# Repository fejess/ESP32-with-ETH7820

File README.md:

# ESP32 with ETH7820AI

SIMPLE project with ETH7820 with ESP32, without PHY power and clock out.
Tested.

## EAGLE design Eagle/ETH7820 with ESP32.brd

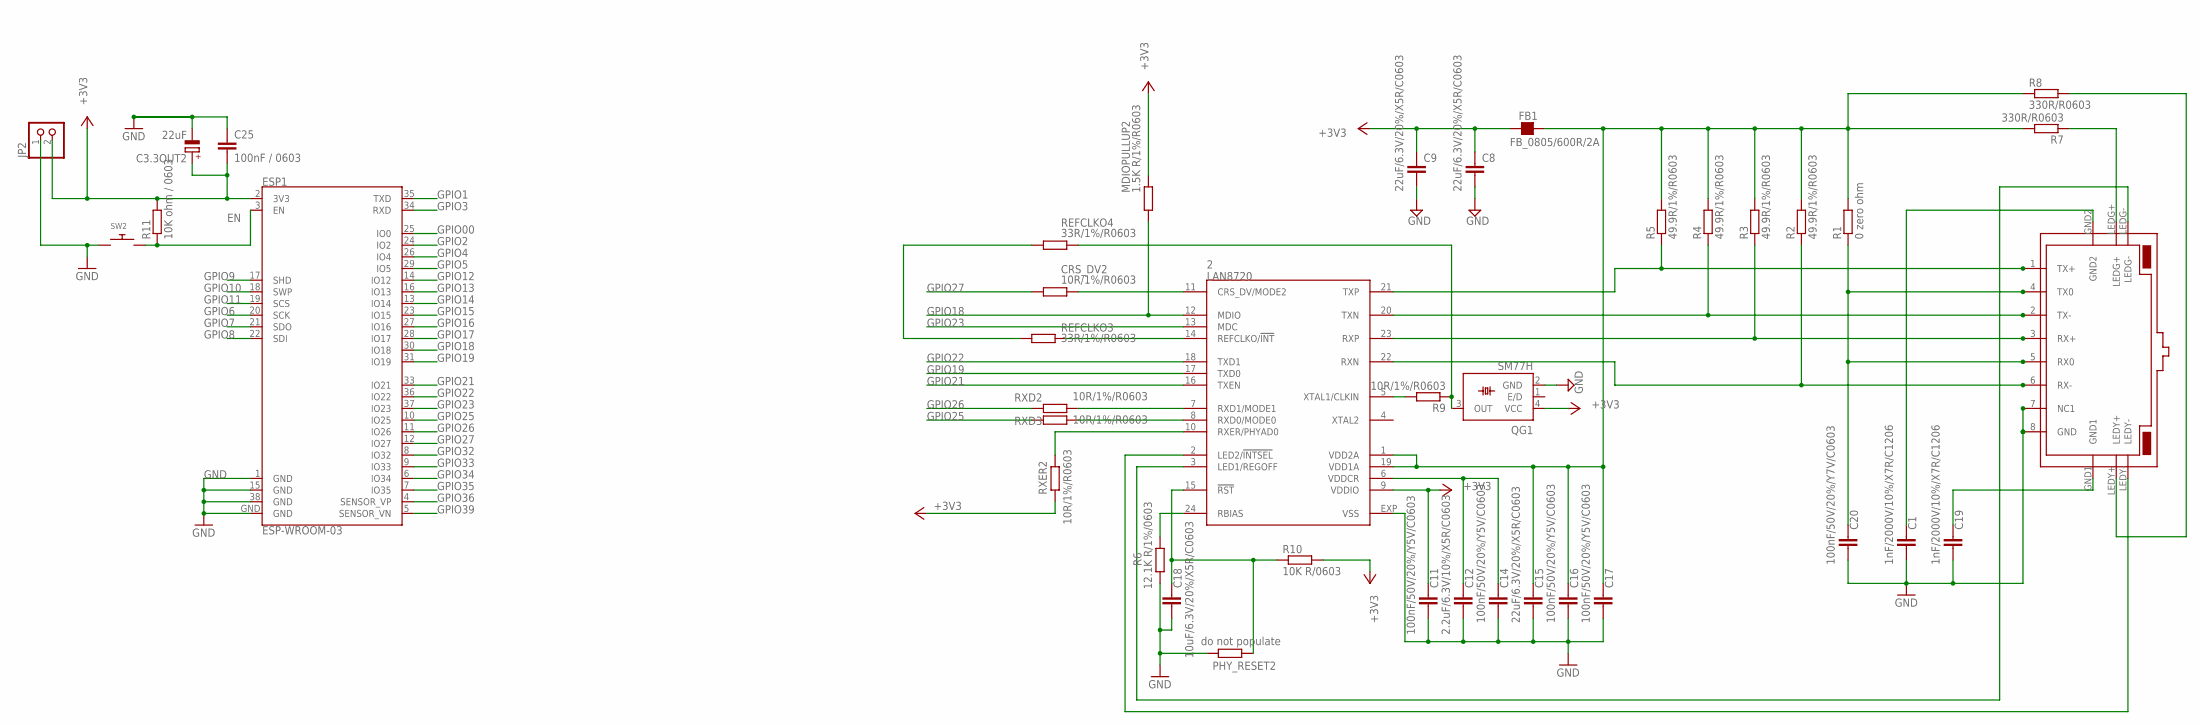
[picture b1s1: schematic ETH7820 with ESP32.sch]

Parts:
2: LAN8720; QFN24
C1, C19: 1nF/2000V/10%/X7R/C1206; C1206
C3.3OUT2: 22uF; 153CLV-0605
C8, C9, C15: 22uF/6.3V/20%/X5R/C0603; C0603
C11, C14, C16, C17: 100nF/50V/20%/Y5V/C0603; C0603
C12: 2.2uF/6.3V/10%/X5R/C0603; C0603
C18: 10uF/6.3V/20%/X5R/C0603; C0603
C20: 100nF/50V/20%/Y7V/C0603; C0603
C25: 100nF / 0603; C0603
CRS_DV2: 10R/1%/R0603; R0603
ESP1: ESP-WROOM-03
FB1: FB_0805/600R/2A; L0805
JP2: PINHD-1X2; 1X02
MDIOPULLUP2: 1.5K R/1%/R0603; R0603
PHY_RESET2: do not populate; R0603
QG1: SM77H
R1: 0 zero ohm; R0603
R2, R3, R4, R5: 49.9R/1%/R0603; R0603
R6: 12.1K R/1%/0603; R0603
R7, R8: 330R/R0603; R0603
R9: 10R/1%/R0603; R0603
R10: 10K R/0603; R0603
R11: 10K ohm / 0603; R0603
REFCLKO3, REFCLKO4: 33R/1%/R0603; R0603
RJ2: RJ45-TRAFO-L
RXD2, RXD3: 10R/1%/R0603; R0603
RXER2: 10R/1%/R0603; R0603
SW2: SWITCH_PUSHBUTTONEVQ-PE; TACT_PANA-EVQ

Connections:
+3V3: 2.9 (VDDIO), C3.3OUT2.+, C8.1, C9.1, C11.1, C25.2, ESP1.2 (3V3), FB1.1, JP2.2, MDIOPULLUP2.2, QG1.4 (VCC), R10.2, R11.2, RXER2.2
EN: ESP1.3 (EN), R11.1, SW2.P$2
GND: 2.EXP (VSS), C1.2, C3.3OUT2.-, C8.2, C9.2, C11.2, C12.2, C14.2, C15.2, C16.2, C17.2, C18.2, C19.2, C20.2, C25.1, ESP1.1 (GND), ESP1.15 (GND), ESP1.38 (GND), ESP1.GND, JP2.1, PHY_RESET2.1, QG1.2 (GND), R6.1, RJ2.7 (NC1), RJ2.8 (GND), SW2.P$1
GPIO00: ESP1.25 (IO0)
GPIO1: ESP1.35 (TXD)
GPIO2: ESP1.24 (IO2)
GPIO3: ESP1.34 (RXD)
GPIO4: ESP1.26 (IO4)
GPIO5: ESP1.29 (IO5)
GPIO6: ESP1.20 (SCK)
GPIO7: ESP1.21 (SDO)
GPIO8: ESP1.22 (SDI)
GPIO9: ESP1.17 (SHD)
GPIO10: ESP1.18 (SWP)
GPIO11: ESP1.19 (SCS)
GPIO12: ESP1.14 (IO12)
GPIO13: ESP1.16 (IO13)
GPIO14: ESP1.13 (IO14)
GPIO15: ESP1.23 (IO15)
GPIO16: ESP1.27 (IO16)
GPIO17: ESP1.28 (IO17)
GPIO18: 2.12 (MDIO), ESP1.30 (IO18), MDIOPULLUP2.1
GPIO19: 2.17 (TXD0), ESP1.31 (IO19)
GPIO21: 2.16 (TXEN), ESP1.33 (IO21)
GPIO22: 2.18 (TXD1), ESP1.36 (IO22)
GPIO23: 2.13 (MDC), ESP1.37 (IO23)
GPIO25: ESP1.10 (IO25), RXD3.1
GPIO26: ESP1.11 (IO26), RXD2.1
GPIO27: CRS_DV2.1, ESP1.12 (IO27)
GPIO32: ESP1.8 (IO32)
GPIO33: ESP1.9 (IO33)
GPIO34: ESP1.6 (IO34)
GPIO35: ESP1.7 (IO35)
GPIO36: ESP1.4 (SENSOR_VP)
GPIO39: ESP1.5 (SENSOR_VN)
unnamed: 2.20 (TXN), R4.1, RJ2.2 (TX-)
unnamed: 2.21 (TXP), R5.1, RJ2.1 (TX+)
unnamed: 2.23 (RXP), R3.1, RJ2.3 (RX+)
unnamed: 2.24 (RBIAS), R6.2
unnamed: 2.2 (LED2/!INTSEL), RJ2.LEDY-
unnamed: 2.22 (RXN), R2.1, RJ2.6 (RX-)
unnamed: 2.1 (VDD2A), 2.19 (VDD1A), C15.1, C16.1, C17.1, FB1.2, R1.2, R2.2, R3.2, R4.2, R5.2, R7.2, R8.1
unnamed: 2.6 (VDDCR), C12.1, C14.1
unnamed: 2.5 (XTAL1/CLKIN), R9.2
unnamed: 2.11 (CRS_DV/MODE2), CRS_DV2.2
unnamed: 2.14 (REFCLKO/!INT), REFCLKO3.2
unnamed: 2.7 (RXD1/MODE1), RXD2.2
unnamed: 2.8 (RXD0/MODE0), RXD3.2
unnamed: 2.10 (RXER/PHYAD0), RXER2.1
unnamed: 2.15 (!RST), C18.1, PHY_RESET2.2, R10.1
unnamed: C20.1, R1.1, RJ2.4 (TX0), RJ2.5 (RX0)
unnamed: C19.1, RJ2.GND1
unnamed: C1.1, RJ2.GND2
unnamed: R7.1, RJ2.LEDG+
unnamed: 2.3 (LED1/REGOFF), RJ2.LEDG-
unnamed: REFCLKO3.1, REFCLKO4.1
unnamed: R8.2, RJ2.LEDY+
unnamed: QG1.3 (OUT), R9.1, REFCLKO4.2

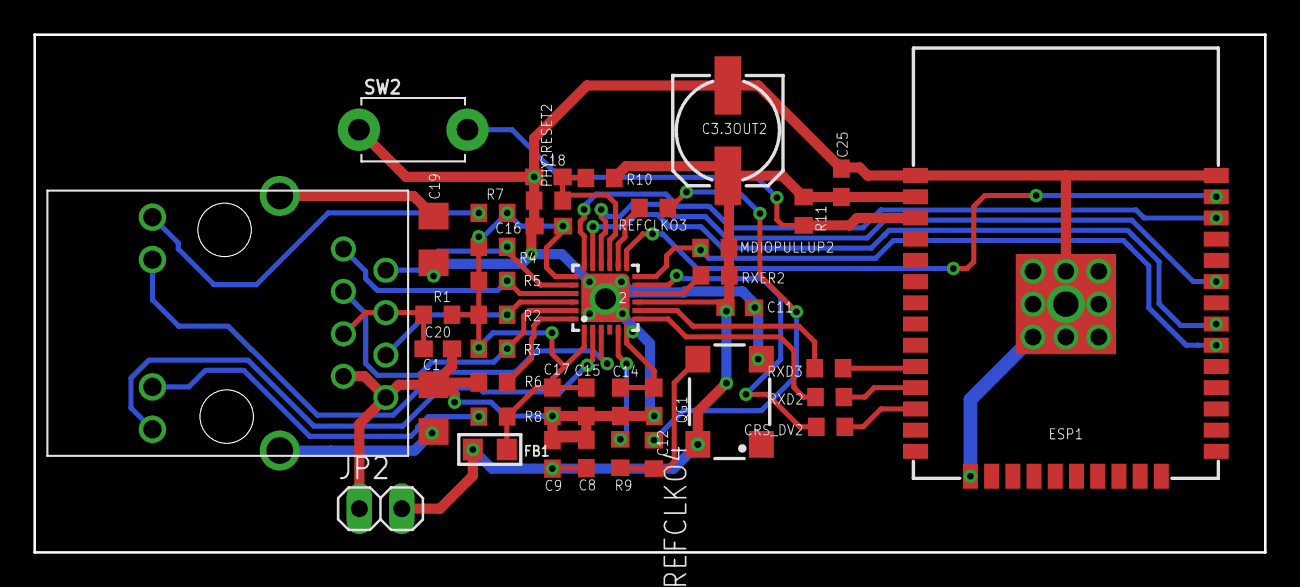
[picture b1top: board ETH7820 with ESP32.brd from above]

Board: 2 copper layers, 73.7 x 31.0 mm, 40 parts (0 on the bottom side), 34 nets.

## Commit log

2018-08-07 changed folder name
2018-10-26 board renew
2018-11-03 pics

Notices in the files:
parts and their libraries:
microchip-smsc-lan8720: (C) 2014 Tomasz Boleslaw CEDRO, cederom@tlen.pl, http://www.tomek.cedro.info.
rc-master-smd: Copyright (C) 2007, Bob Starr
